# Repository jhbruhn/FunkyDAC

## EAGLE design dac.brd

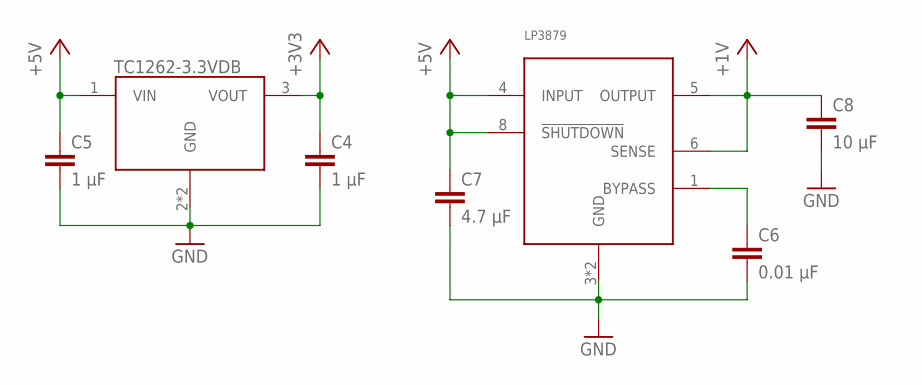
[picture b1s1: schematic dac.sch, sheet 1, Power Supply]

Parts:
C4, C5: 1 µF; C0402; MPN MC0805B104K500A5.08MM
C6: 0.01 µF; C0402; MPN MC0805B104K500A5.08MM
C7: 4.7 µF; C0402; MPN MC0805B104K500A5.08MM
C8: 10 µF; C0402; MPN MC0805B104K500A5.08MM
IC2: TC1262-3.3VDB; SOT223
IC3: LP3879; SO08

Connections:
+1V: C8.1, IC3.5 (OUTPUT), IC3.6 (SENSE); also elsewhere on the board
+3V3: C4.1, IC2.3 (VOUT); also elsewhere on the board
+5V: C5.1, C7.1, IC2.1 (VIN), IC3.4 (INPUT), IC3.8 (!SHUTDOWN); also elsewhere on the board
GND: C4.2, C5.2, C6.2, C7.2, C8.2, IC2.2 (GND), IC2.4 (GND), IC3.3 (GND), IC3.P$1 (GND); also elsewhere on the board
unnamed: C6.1, IC3.1 (BYPASS)

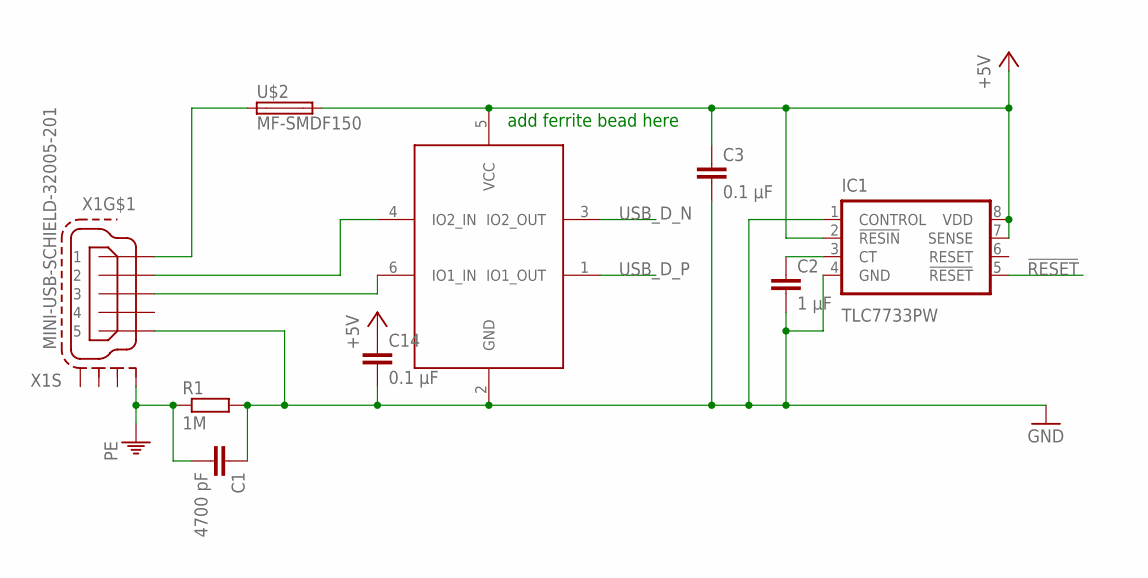
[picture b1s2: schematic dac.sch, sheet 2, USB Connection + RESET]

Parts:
C1: 4700 pF; C0402; MPN 08055C472KAT2A
C2: 1 µF; C0402; MPN MC0805B104K500A5.08MM
C3, C14: 0.1 µF; C0402; MPN 0402N101J500CT
IC1: TLC7733PW; PW_R-PDSO-G08
IC5: RCLAMP0502ASMD; SOT666
R1: 1M; R0402; MPN CRCW20101M00FKEF
U$2: MF-SMDF150; MF-SMDF050; MPN MF-SMDF150-2
X1: MINI-USB-SCHIELD-32005-201; 32005-201

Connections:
!RESET: IC1.5 (!RESET); also elsewhere on the board
+5V: C3.1, C14.1, IC1.2 (!RESIN), IC1.7 (SENSE), IC1.8 (VDD), IC5.5 (VCC), U$2.2; also elsewhere on the board
GND: C1.1, C2.2, C3.2, C14.2, IC1.1 (CONTROL), IC1.4 (GND), IC5.2 (GND), R1.2, X1.5; also elsewhere on the board
unnamed: U$2.1, X1.1
unnamed: IC5.4 (IO2_IN), X1.2
unnamed: IC5.6 (IO1_IN), X1.3
unnamed: C2.1, IC1.3 (CT)
PE: C1.2, R1.1, X1.M1 (S1)
USB_D_N: IC5.3 (IO2_OUT); also elsewhere on the board
USB_D_P: IC5.1 (IO1_OUT); also elsewhere on the board

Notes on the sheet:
add ferrite bead here

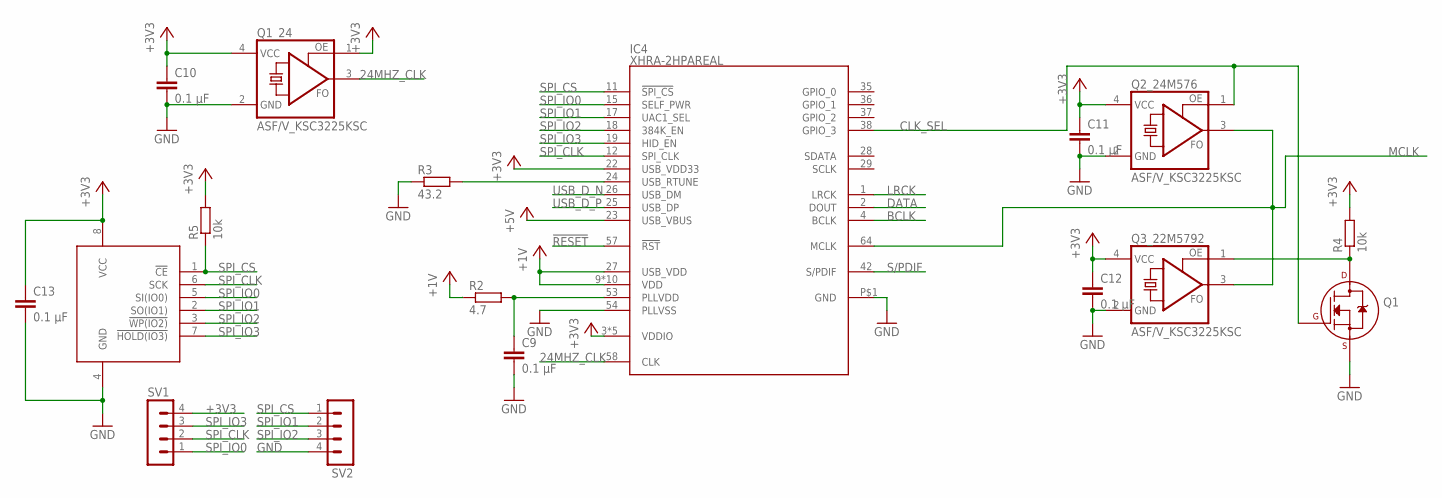
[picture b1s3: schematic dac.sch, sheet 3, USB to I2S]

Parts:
C9: 0.1 µF; C0402
C10, C11, C12, C13: 0.1 µF; C0402; MPN 0402N101J500CT
IC4: XHRA-2HPAREAL; TQFP64-10X10
Q1: 2N7002_SOT23; SOT-23
Q1_24, Q2_24M576, Q3_22M5792: ASF/V_KSC3225KSC; KSC
R2: 4.7; R0402
R3: 43.2; R0402
R4, R5: 10k; R0402
SV1, SV2: MA04-1
U$1: S25FL116K; SO8

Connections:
24MHZ_CLK: IC4.58 (CLK), Q1_24.3 (FO)
!RESET: IC4.57 (!RST); also elsewhere on the board
+1V: IC4.9 (VDD), IC4.10 (VDD), IC4.20 (VDD), IC4.27 (USB_VDD), IC4.31 (VDD), IC4.39 (VDD), IC4.40 (VDD), IC4.41 (VDD), IC4.52 (VDD), IC4.56 (VDD), IC4.59 (VDD), R2.1; also elsewhere on the board
+3V3: C10.1, C11.1, C12.1, C13.1, IC4.3 (VDDIO), IC4.13 (VDDIO), IC4.22 (USB_VDD33), IC4.34 (VDDIO), IC4.44 (VDDIO), IC4.55 (VDDIO), Q1_24.1 (OE), Q1_24.4 (VCC), Q2_24M576.4 (VCC), Q3_22M5792.4 (VCC), R4.2, R5.2, SV1.4, U$1.8 (VCC); also elsewhere on the board
+5V: IC4.23 (USB_VBUS); also elsewhere on the board
BCLK: IC4.4 (BCLK); also elsewhere on the board
CLK_SEL: IC4.38 (GPIO_3), Q1.1 (G), Q2_24M576.1 (OE)
DATA: IC4.2 (DOUT)
GND: C9.2, C10.2, C11.2, C12.2, C13.2, IC4.54 (PLLVSS), IC4.P$1 (GND), Q1.2 (S), Q1_24.2 (GND), Q2_24M576.2 (GND), Q3_22M5792.2 (GND), R3.1, SV2.4, U$1.4 (GND); also elsewhere on the board
LRCK: IC4.1 (LRCK)
MCLK: IC4.64 (MCLK), Q2_24M576.3 (FO), Q3_22M5792.3 (FO)
unnamed: C9.1, IC4.53 (PLLVDD), R2.2
unnamed: IC4.24 (USB_RTUNE), R3.2
unnamed: Q1.3 (D), Q3_22M5792.1 (OE), R4.1
S/PDIF: IC4.42 (S/PDIF)
SPI_CLK: IC4.12 (SPI_CLK), SV1.2, U$1.6 (SCK)
SPI_CS: IC4.11 (!SPI_CS), R5.1, SV2.1, U$1.1 (!CE)
SPI_IO0: IC4.15 (SELF_PWR), SV1.1, U$1.5 (SI(IO0))
SPI_IO1: IC4.17 (UAC1_SEL), SV2.2, U$1.2 (SO(IO1))
SPI_IO2: IC4.18 (384K_EN), SV2.3, U$1.3 (!WP(IO2))
SPI_IO3: IC4.19 (HID_EN), SV1.3, U$1.7 (!HOLD(IO3))
USB_D_N: IC4.26 (USB_DM); also elsewhere on the board
USB_D_P: IC4.25 (USB_DP); also elsewhere on the board

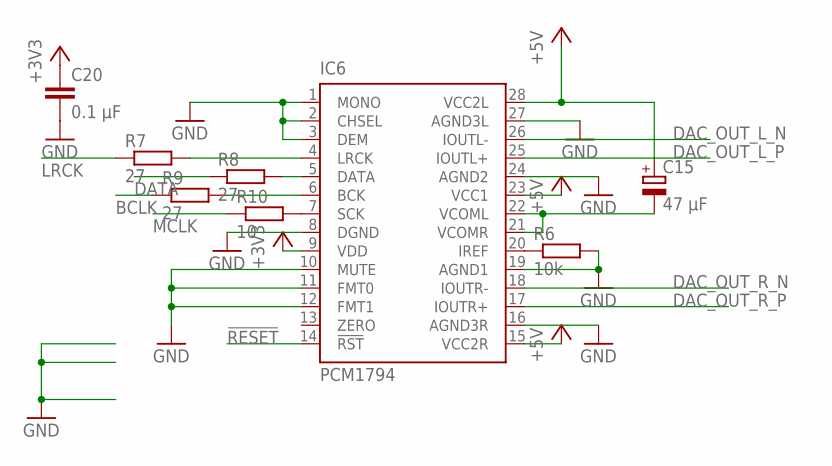
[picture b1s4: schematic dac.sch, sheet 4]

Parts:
C15: 47 µF; 140CLH-0810
C20: 0.1 µF; C0402; MPN 0402N101J500CT
IC6: PCM1794; DB_R-PDSO-G28
R6: 10k; R0603
R7, R8, R9: 27; R0603
R10: 10; R0603

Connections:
!RESET: IC6.14 (!RST); also elsewhere on the board
+3V3: C20.1, IC6.9 (VDD); also elsewhere on the board
+5V: C15.+, IC6.15 (VCC2R), IC6.23 (VCC1), IC6.28 (VCC2L); also elsewhere on the board
BCLK: R9.1; also elsewhere on the board
DAC_OUT_L_N: IC6.26 (IOUTL-); also elsewhere on the board
DAC_OUT_L_P: IC6.25 (IOUTL+); also elsewhere on the board
DAC_OUT_R_N: IC6.18 (IOUTR-); also elsewhere on the board
DAC_OUT_R_P: IC6.17 (IOUTR+); also elsewhere on the board
GND: C20.2, IC6.1 (MONO), IC6.2 (CHSEL), IC6.3 (DEM), IC6.8 (DGND), IC6.10 (MUTE), IC6.11 (FMT0), IC6.12 (FMT1), IC6.16 (AGND3R), IC6.19 (AGND1), IC6.24 (AGND2), IC6.27 (AGND3L), R6.2; also elsewhere on the board
unnamed: C15.-, IC6.21 (VCOMR), IC6.22 (VCOML)
unnamed: IC6.4 (LRCK), R7.2
unnamed: IC6.20 (IREF), R6.1
unnamed: IC6.5 (DATA), R8.2
unnamed: IC6.6 (BCK), R9.2
unnamed: IC6.7 (SCK), R10.2

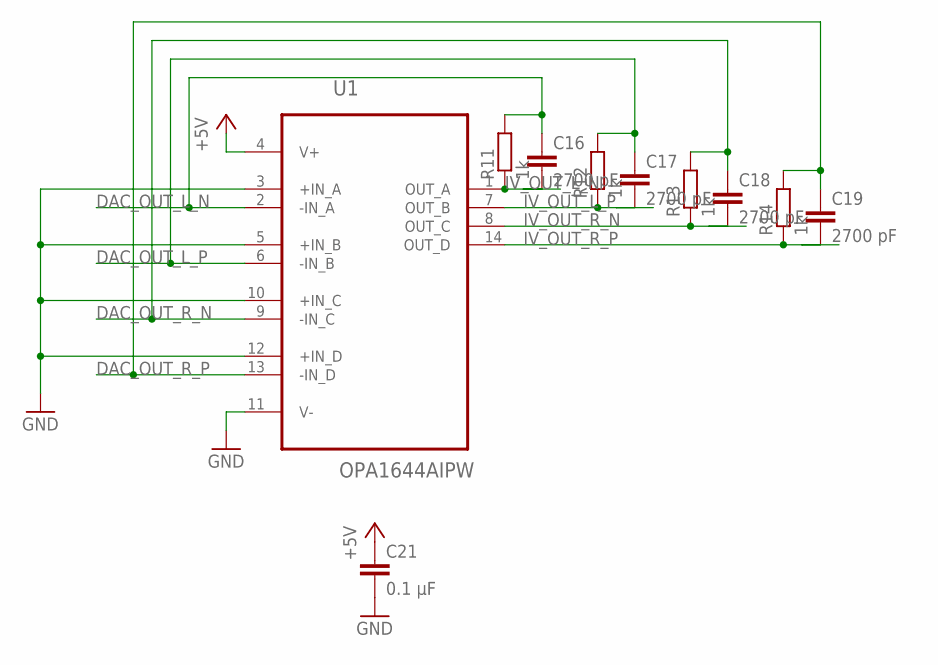
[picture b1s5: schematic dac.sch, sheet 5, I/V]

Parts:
C16, C17, C18, C19: 2700 pF; C0603
C21: 0.1 µF; C0603
R11, R12, R13, R14: 1k; R0603
U1: OPA1644AIPW; SOP65P640X120-14N

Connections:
+5V: C21.1, U1.4 (V+); also elsewhere on the board
DAC_OUT_L_N: C16.1, R11.2, U1.2 (-IN_A); also elsewhere on the board
DAC_OUT_L_P: C17.1, R12.2, U1.6 (-IN_B); also elsewhere on the board
DAC_OUT_R_N: C18.1, R13.2, U1.9 (-IN_C); also elsewhere on the board
DAC_OUT_R_P: C19.1, R14.2, U1.13 (-IN_D); also elsewhere on the board
GND: C21.2, U1.3 (+IN_A), U1.5 (+IN_B), U1.10 (+IN_C), U1.11 (V-), U1.12 (+IN_D); also elsewhere on the board
IV_OUT_L_N: C16.2, R11.1, U1.1 (OUT_A); also elsewhere on the board
IV_OUT_L_P: C17.2, R12.1, U1.7 (OUT_B); also elsewhere on the board
IV_OUT_R_N: C18.2, R13.1, U1.8 (OUT_C); also elsewhere on the board
IV_OUT_R_P: C19.2, R14.1, U1.14 (OUT_D); also elsewhere on the board

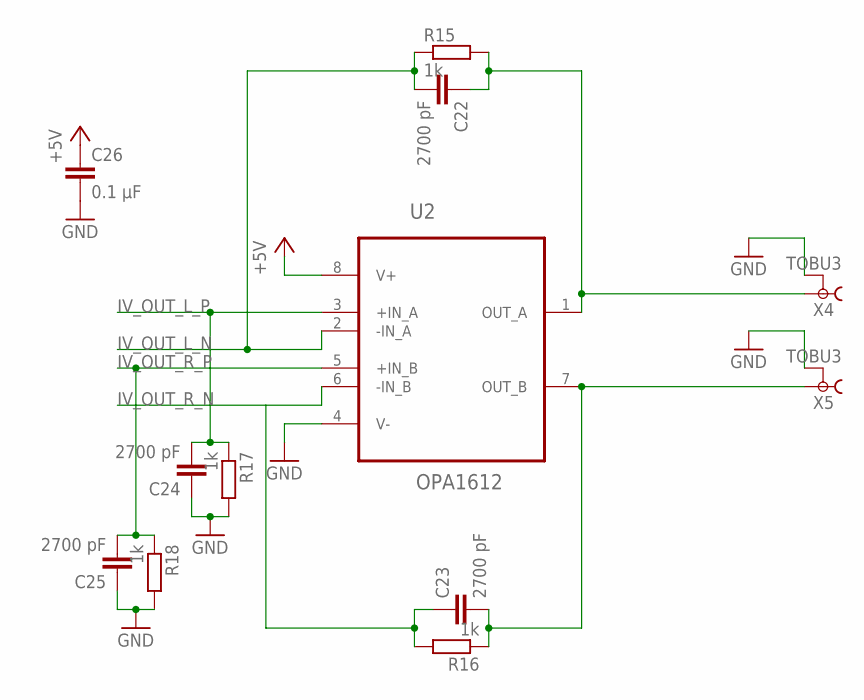
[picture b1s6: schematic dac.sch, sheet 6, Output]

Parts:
C22, C23, C24, C25: 2700 pF; C0603
C26: 0.1 µF; C0603
R15, R16, R17, R18: 1k; R0603
U2: OPA1612; SO8
X4, X5: TOBU3

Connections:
+5V: C26.1, U2.8 (V+); also elsewhere on the board
GND: C24.1, C25.1, C26.2, R17.2, R18.2, U2.4 (V-), X4.2, X4.2@1 (2), X4.2@2 (2), X5.2, X5.2@1 (2), X5.2@2 (2); also elsewhere on the board
IV_OUT_L_N: C22.2, R15.1, U2.2 (-IN_A); also elsewhere on the board
IV_OUT_L_P: C24.2, R17.1, U2.3 (+IN_A); also elsewhere on the board
IV_OUT_R_N: C23.1, R16.2, U2.6 (-IN_B); also elsewhere on the board
IV_OUT_R_P: C25.2, R18.1, U2.5 (+IN_B); also elsewhere on the board
unnamed: C22.1, R15.2, U2.1 (OUT_A), X4.1
unnamed: C23.2, R16.1, U2.7 (OUT_B), X5.1

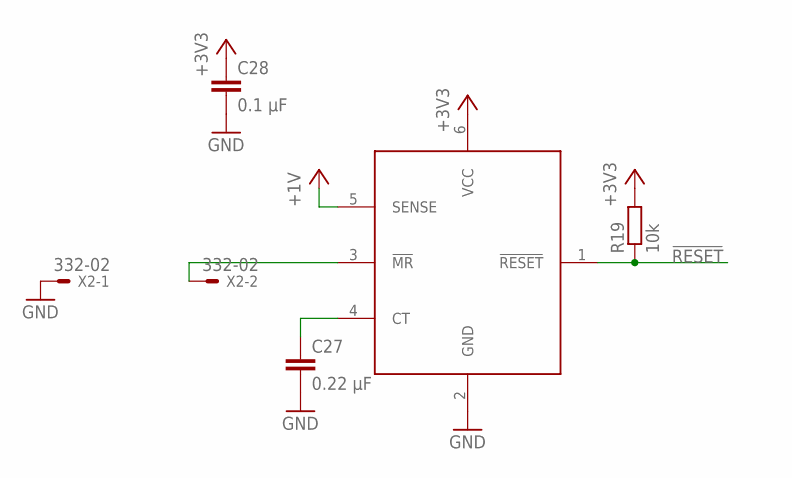
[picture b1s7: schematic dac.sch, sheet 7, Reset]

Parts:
C27: 0.22 µF; C0603
C28: 0.1 µF; C0603
R19: 10k; R0603
U$4: TPS3808; SOT23-6
X2: 332-02

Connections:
!RESET: R19.1, U$4.1 (!RESET); also elsewhere on the board
+1V: U$4.5 (SENSE); also elsewhere on the board
+3V3: C28.1, R19.2, U$4.6 (VCC); also elsewhere on the board
GND: C27.2, C28.2, U$4.2 (GND), X2.1; also elsewhere on the board
unnamed: C27.1, U$4.4 (CT)
unnamed: U$4.3 (!MR), X2.2

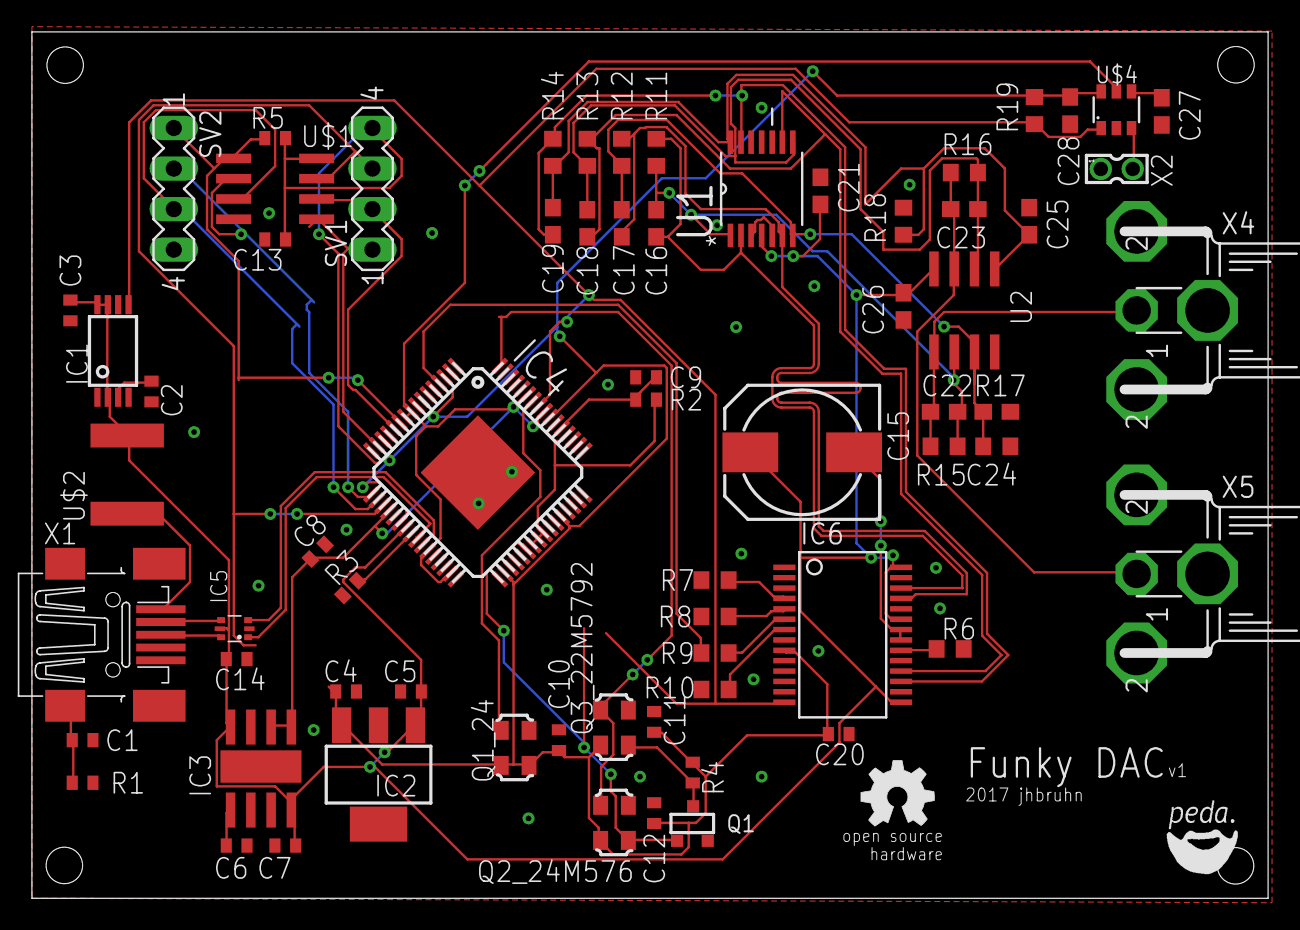
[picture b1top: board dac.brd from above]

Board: 2 copper layers, 77.5 x 54.3 mm, 69 parts (0 on the bottom side), 44 nets.

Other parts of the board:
U$3: OSHW_5MM

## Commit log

2017-10-01 :boom::camel: Added .gitattributes & .gitignore files
2017-10-01 Add Files
2017-10-20 Fix wrong XHRA-2HPA package size
